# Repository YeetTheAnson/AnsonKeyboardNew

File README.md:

# Anson's Keyboard
This is a generic looking 80% TKL keyboard I made over the span of a month. In total, I've spent about 20-25 hours in total for PCB redesigns, writing the keyboard firmware and case redesigns.

## Features
- Individually backlit keys with software addressable RGB
- 0.91" OLED display
- USB and Bluetooth connectivity

### LED Control
The keyboard has three LED modes:
1. **Off Mode**: All LEDs are turned off
2. **RGB Mode**: LEDs display a rainbow effect
3. **Custom Color Mode**: All LEDs use a user-defined color

### LED Mode Controls
* **Toggle LED Mode**: `Ctrl + Alt + Pause/Break`
   * Cycles through Off → RGB → Custom Color
* **Adjust Brightness Up**: `Ctrl + Alt + Shift + Up Arrow`
* **Adjust Brightness Down**: `Ctrl + Alt + Shift + Down Arrow`

### Custom Color Configuration
1. **Enter Custom Color Mode**: `Ctrl + Alt + Page Up`
2. When in custom color mode:
   * The OLED will prompt for R, G, and B values sequentially
   * Use number keys (0-9) to enter a value between 0-255
   * Press `Backspace` to delete the last digit
   * Press `Enter` to confirm and move to the next color component
   * After setting all three RGB values, the keyboard returns to normal operation with your custom color

### Bluetooth Functionality
The keyboard can operate in either USB or Bluetooth mode:
* **Check Current Mode**: The OLED screen displays either "USB Mode" or "BT Mode"
* **Switch to Bluetooth Mode**: Hold the Pause/Break key during boot (pin IO36)
   * Note: After setup, the keyboard will remain in Bluetooth mode until changed

### OLED Display
The OLED display shows:
1. "AnsonKeyboard"
2. Connection mode (USB or Bluetooth)
3. Current WPM (words per minute) typing speed
4. Current LED mode

When in custom color configuration mode, the display shows prompts for entering RGB values.

### Performance Monitoring
The keyboard automatically calculates your typing speed (WPM) and displays it on the OLED screen. This is calculated based on:
* Number of keypresses
* Time elapsed since last keypress
* Standard conversion (5 characters = 1 word)

### Special Key Combinations
| Function | Key Combination |
|----------|----------------|
| Toggle LED Mode | Ctrl + Alt + Pause/Break |
| Enter Custom Color Mode | Ctrl + Alt + Page Up |
| Increase LED Brightness | Ctrl + Alt + Shift + Up Arrow |
| Decrease LED Brightness | Ctrl + Alt + Shift + Down Arrow |
| Enter Bluetooth Mode | Hold Pause/Break during boot |

## Design Process
I started with a simple idea which was a flat minimalistic TKL keyboard (inspired by the Apple keyboard). The goal was to keep it clean and 
modern, and remove unnecessary designs. However, as I thought more about ergonomics, I quickly realized that a completely flat keyboard wouldn't be comfortable at all
to use during typing.

My initial PCB design had borders that were too thick, which also made the case borders too thick, it was quite bulky and uglier than what I wanted

I originally planned to use the Orpheus Pico as the microcontroller. However, due to the large footprint (making the case even bulkier) and the lack of wireless connectivity, I scrapped that idea
and moved on to a new design. At this point, I also decided to make a triangle wedge to set the keyboard at 6 degrees for a better typing experience.

I wanted an integrated USB C port directly on the PCB, but when I redesigned the case and PCB to fit it, I realized that it would be close to impossible for someone with my skill level to hand solder the USB C port and it
would have stuck up at an angle anyway (this stresses the cable)

For the final design, I came up a solution. Instead of mounting the USB C port directly onto the PCB, I would purchase a USB C breakout board instead and connect it via cables to the PCB. 

(This is when the routing hell begins as I reroute the entire thing at least 3 times)
The first time was my extremely inefficient matrix which was a 8x11 matrix. The traces were extremely messy and I've counted about 1.1k traces and 500 vias in total. (I'm so glad I don't have to see it again). I've then updated it to a 7x14 matrix which made routing much easier.
The second time was when I had to move all LEDs down by 2mm since they didn't align with the cutout in the switches.
Not even an hour after posting about my rerouting, someone from Slack recommmended that I wire my LEDs from top to bottom instead of side to side as to reduce via usage. This is the current version of the PCB and I'm quite happy with it

# Pictures
## Schematic

## PCB

## Renders

## Case Stand (CaseStand.step)

## Lower Case (LowerCase.step)

## Plate (Plate.step)

## Top Case (TopCase.step)

# Bill Of Material

## Electronics (LCSC)

### Passive Components

| QTY  | Name          | Part Number         | LCSC Part Number | Price |
|------|--------------|---------------------|------------------|-------|
| 100x | 4.7kΩ Resistor | 1206W4F4701T5E     | [C17936](https://www.lcsc.com/product-detail/Chip-Resistor-Surface-Mount_UNI-ROYAL-Uniroyal-Elec-1206W4F4701T5E_C17936.html) | $0.32 |
| 100x | 5.1kΩ Resistor | 1206W4F5101T5E     | [C26033](https://www.lcsc.com/product-detail/Chip-Resistor-Surface-Mount_UNI-ROYAL-Uniroyal-Elec-1206W4F5101T5E_C26033.html) | $0.32 |
| 20x  | Tact Switch   | TS-1187A-B-A-B      | [C318884](https://www.lcsc.com/product-detail/Tactile-Switches_XKB-Connection-TS-1187A-B-A-B_C318884.html) | $0.38 |
| 5x   | 3.3v Regulator | AMS1117-3.3        | [C6186](https://www.lcsc.com/product-detail/Voltage-Regulators-Linear-Low-Drop-Out-LDO-Regulators_Advanced-Monolithic-Systems-AMS1117-3-3_C6186.html) | $0.84 |
| 150x | 100nF Capacitor | CC1206KRX7R9BB104  | [C82601](https://www.lcsc.com/product-detail/Multilayer-Ceramic-Capacitors-MLCC-SMD-SMT_YAGEO-CC1206KRX7R9BB104_C82601.html) | $1.61 |
| 20x  | 10uF Capacitor | CL31B106KAHNNNE    | [C14860](https://www.lcsc.com/product-detail/Multilayer-Ceramic-Capacitors-MLCC-SMD-SMT_Samsung-Electro-Mechanics-CL31B106KAHNNNE_C14860.html) | $0.54 |
| 200x | Diode         | 1N4148WL            | [C33962554](https://www.lcsc.com/product-detail/Diodes-General-Purpose_Slkor-SLKORMICRO-Elec-1N4148WL_C33962554.html) | $1.00 |

### Active Components

| QTY  | Name         | Part Number          | LCSC Part Number | Price |
|------|-------------|----------------------|------------------|-------|
| 150x | RGB LED     | SK6812MINI-E         | [C5149201](https://www.lcsc.com/product-detail/RGB-LEDs-Built-in-IC_OPSCO-Optoelectronics-SK6812MINI-E_C5149201.html) | $8.70 |
| 1x   | ESP-32-S3   | ESP32-S3-WROOM-1-N16R2 | [C2913205](https://www.lcsc.com/product-detail/WiFi-Modules_Espressif-Systems-ESP32-S3-WROOM-1-N16R2_C2913205.html) | $5.04 |
| 10x  | Level Shifter | SN74LV1T34DBVR      | [C100024](https://www.lcsc.com/product-detail/Buffers-Drivers-Receivers-Transceivers_Texas-Instruments-SN74LV1T34DBVR_C100024.html) | $0.59 |

**LCSC Shipping**: Singapore Post – $5.72  

## Electronics (Local Vendor. I will be paying for these)

| QTY  | Name | Local Price | Conversion Upcharge | Price |
|------|------|------------|---------------------|-------|
| 5x   | [USB C Breakout Board](https://shopee.com.my/product/145270449/29272008539) | RM8.13 | +$0.15 | $2.10 |
| 1x  | [0.91" OLED](https://shopee.com.my/product/145270449/4639327724) | RM10.62 | +$0.15 | $2.65 |
| 1x   | SPX Express Shipping | RM5.20 | +$0.15 | $1.40 |

---

## Production  

| QTY  | Name       | File Name      | Production Method | Price  |
|------|-----------|---------------|------------------|--------|
| 1x   | Top Case  | TopCase.step  | FDM 3D Print    | -      |
| 1x   | Plate     | Plate.step    | FDM 3D Print    | -      |
| 1x   | Lower Case | LowerCase.step | FDM 3D Print    | -      |
| 1x   | Case Stand | CaseStand.step | FDM 3D Print    | -      |
| 5x   | PCB       | gerbers.zip   | JLCPCB          | $22.20 |
| 1x   | PCB Shipping | -          | E-Post         | $9.76 |

---

## Fasteners  

| QTY  | Name | Local Price | Conversion Upcharge | Price |
|------|------|------------|---------------------|-------|
| 27x  | [M2 x 3.5 x 4 Heat Set Insert](https://shopee.com.my/-M2-M2.5-M3-Helical-Knurled-Embedded-Nut-Heat-Set-Threaded-Insert-3D-Printing-Injection-Molding-Laptop-Repair-Brass-i.327548229.21958741418) | RM9.45 | +$0.15 | $2.39 |
| 12x  | [M2 x 3.5 x 2 Heat Set Insert](https://shopee.com.my/-M2-M2.5-M3-Helical-Knurled-Embedded-Nut-Heat-Set-Threaded-Insert-3D-Printing-Injection-Molding-Laptop-Repair-Brass-i.327548229.21958741418) | RM4.20 | +$0.15 | $1.14 |
| 12x  | [M2 x 5mm Hex Screw](https://shopee.com.my/M2-M2.5-Hex-Socket-Button-Head-Cap-Screw-Allen-Key-Bolt-Skru-Stainless-Steel-304-i.327548229.14990997313) | RM4.56 | +$0.15 | $1.23 |
| 12x  | [M2 x 3mm Hex Screw](https://shopee.com.my/M2-M2.5-Hex-Socket-Button-Head-Cap-Screw-Allen-Key-Bolt-Skru-Stainless-Steel-304-i.327548229.14990997313) | RM4.08 | +$0.15 | $1.12 |
| 15x  | [M2 x 12mm Hex Screw](https://shopee.com.my/M2-M2.5-Hex-Socket-Button-Head-Cap-Screw-Allen-Key-Bolt-Skru-Stainless-Steel-304-i.327548229.14990997313) | RM6.90 | +$0.15 | $1.78 |
| 1x   | SPX Express Shipping | RM10.60 | +$0.15 | $2.66 |

---

## Mechanical  

| QTY  | Name | Local Price | Conversion Upcharge | Price |
|------|------|------------|---------------------|-------|
| 1x   | [XDA Keycap Set](https://shopee.com.my/MKB-Cinnamoroll-Sanrio-PBT-XDA-Profile-Keycap-Set-for-Mechanical-Keyboard-i.72068395.18262626381?sp_atk=5d020f62-27a6-4ec2-9bfb-f2d231a9ee17&xptdk=5d020f62-27a6-4ec2-9bfb-f2d231a9ee17) | RM91.20 | +$2.50 | $24.14 |
| 1x   | [TX Almost Perfect Stabilizers](https://shopee.com.my/product/72068395/18489170375) | RM74.80 | +$2.50 | $20.25 |
| 91x  | [Gateron Smoothie Switches](https://shopee.com.my/product/72068395/14635071158) | RM136.50 | +$4.00 | $35.42 |
| 1x   | SPX Express Shipping | RM17.00 | +$0.40  | $4.31 |

---

## Total Costs  

- **LCSC Total**: $25.06  
- **Electronics (Local) Total**: $6.15
- **JLCPCB Total**: $31.96  
- **Fasteners Total**: $10.32  
- **Mechanical Total**: $84.12  

## **Grand Total: $157.61**

**Note:** Conversion upcharge is just a buffer for conversion rate fluctuations. Any unused funds will be returned.

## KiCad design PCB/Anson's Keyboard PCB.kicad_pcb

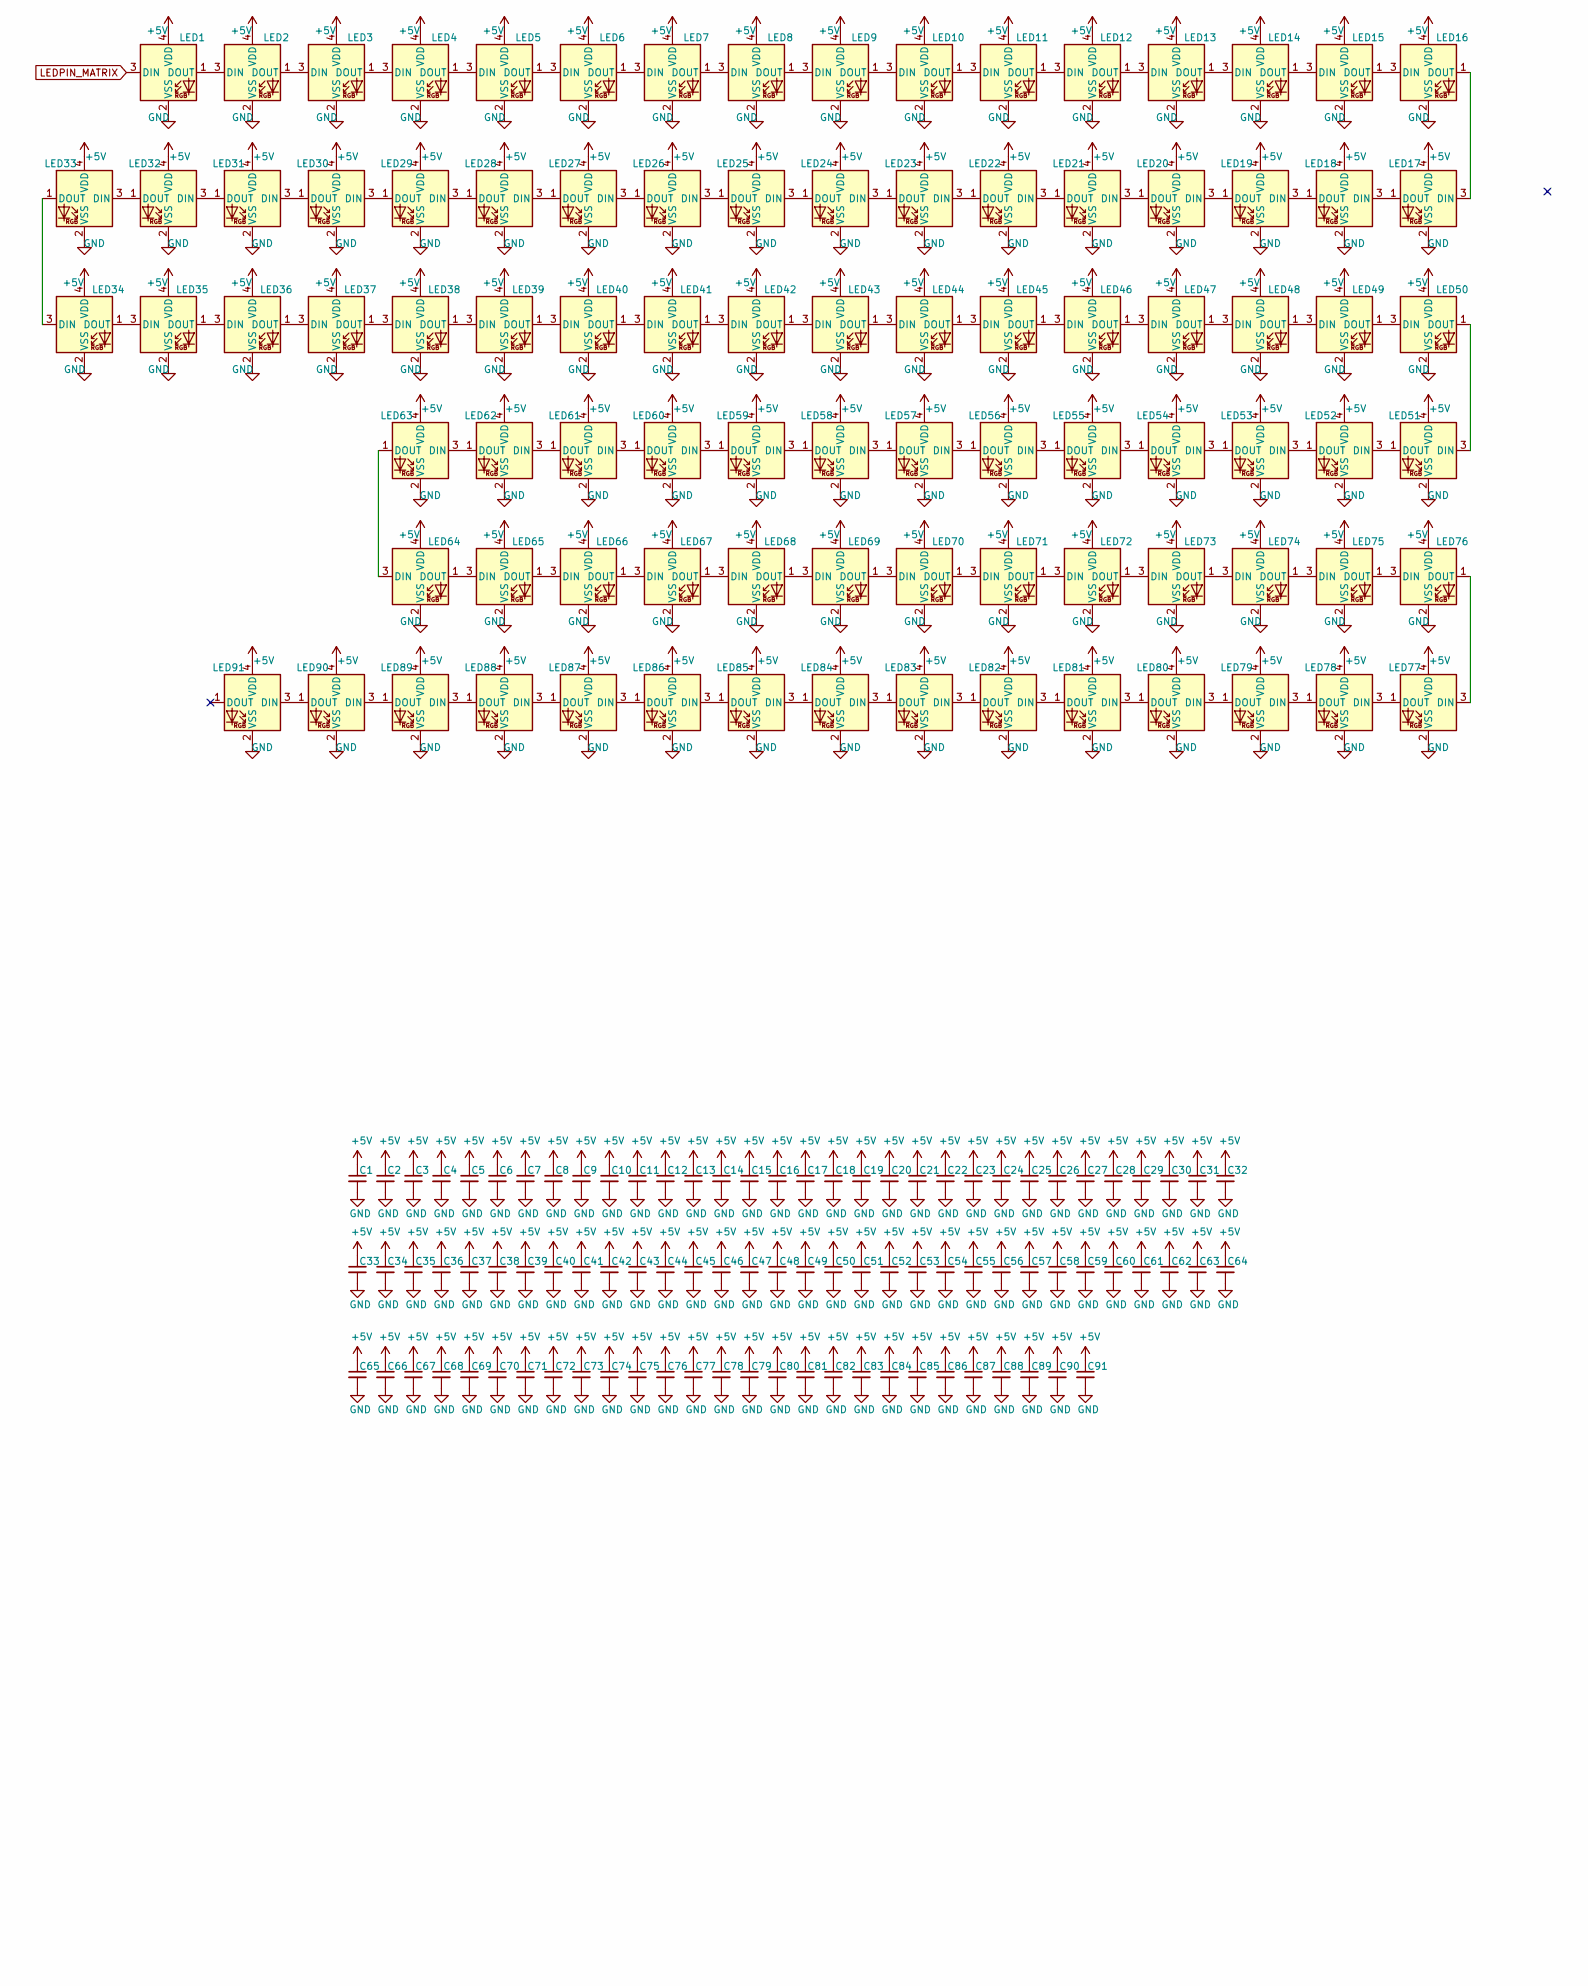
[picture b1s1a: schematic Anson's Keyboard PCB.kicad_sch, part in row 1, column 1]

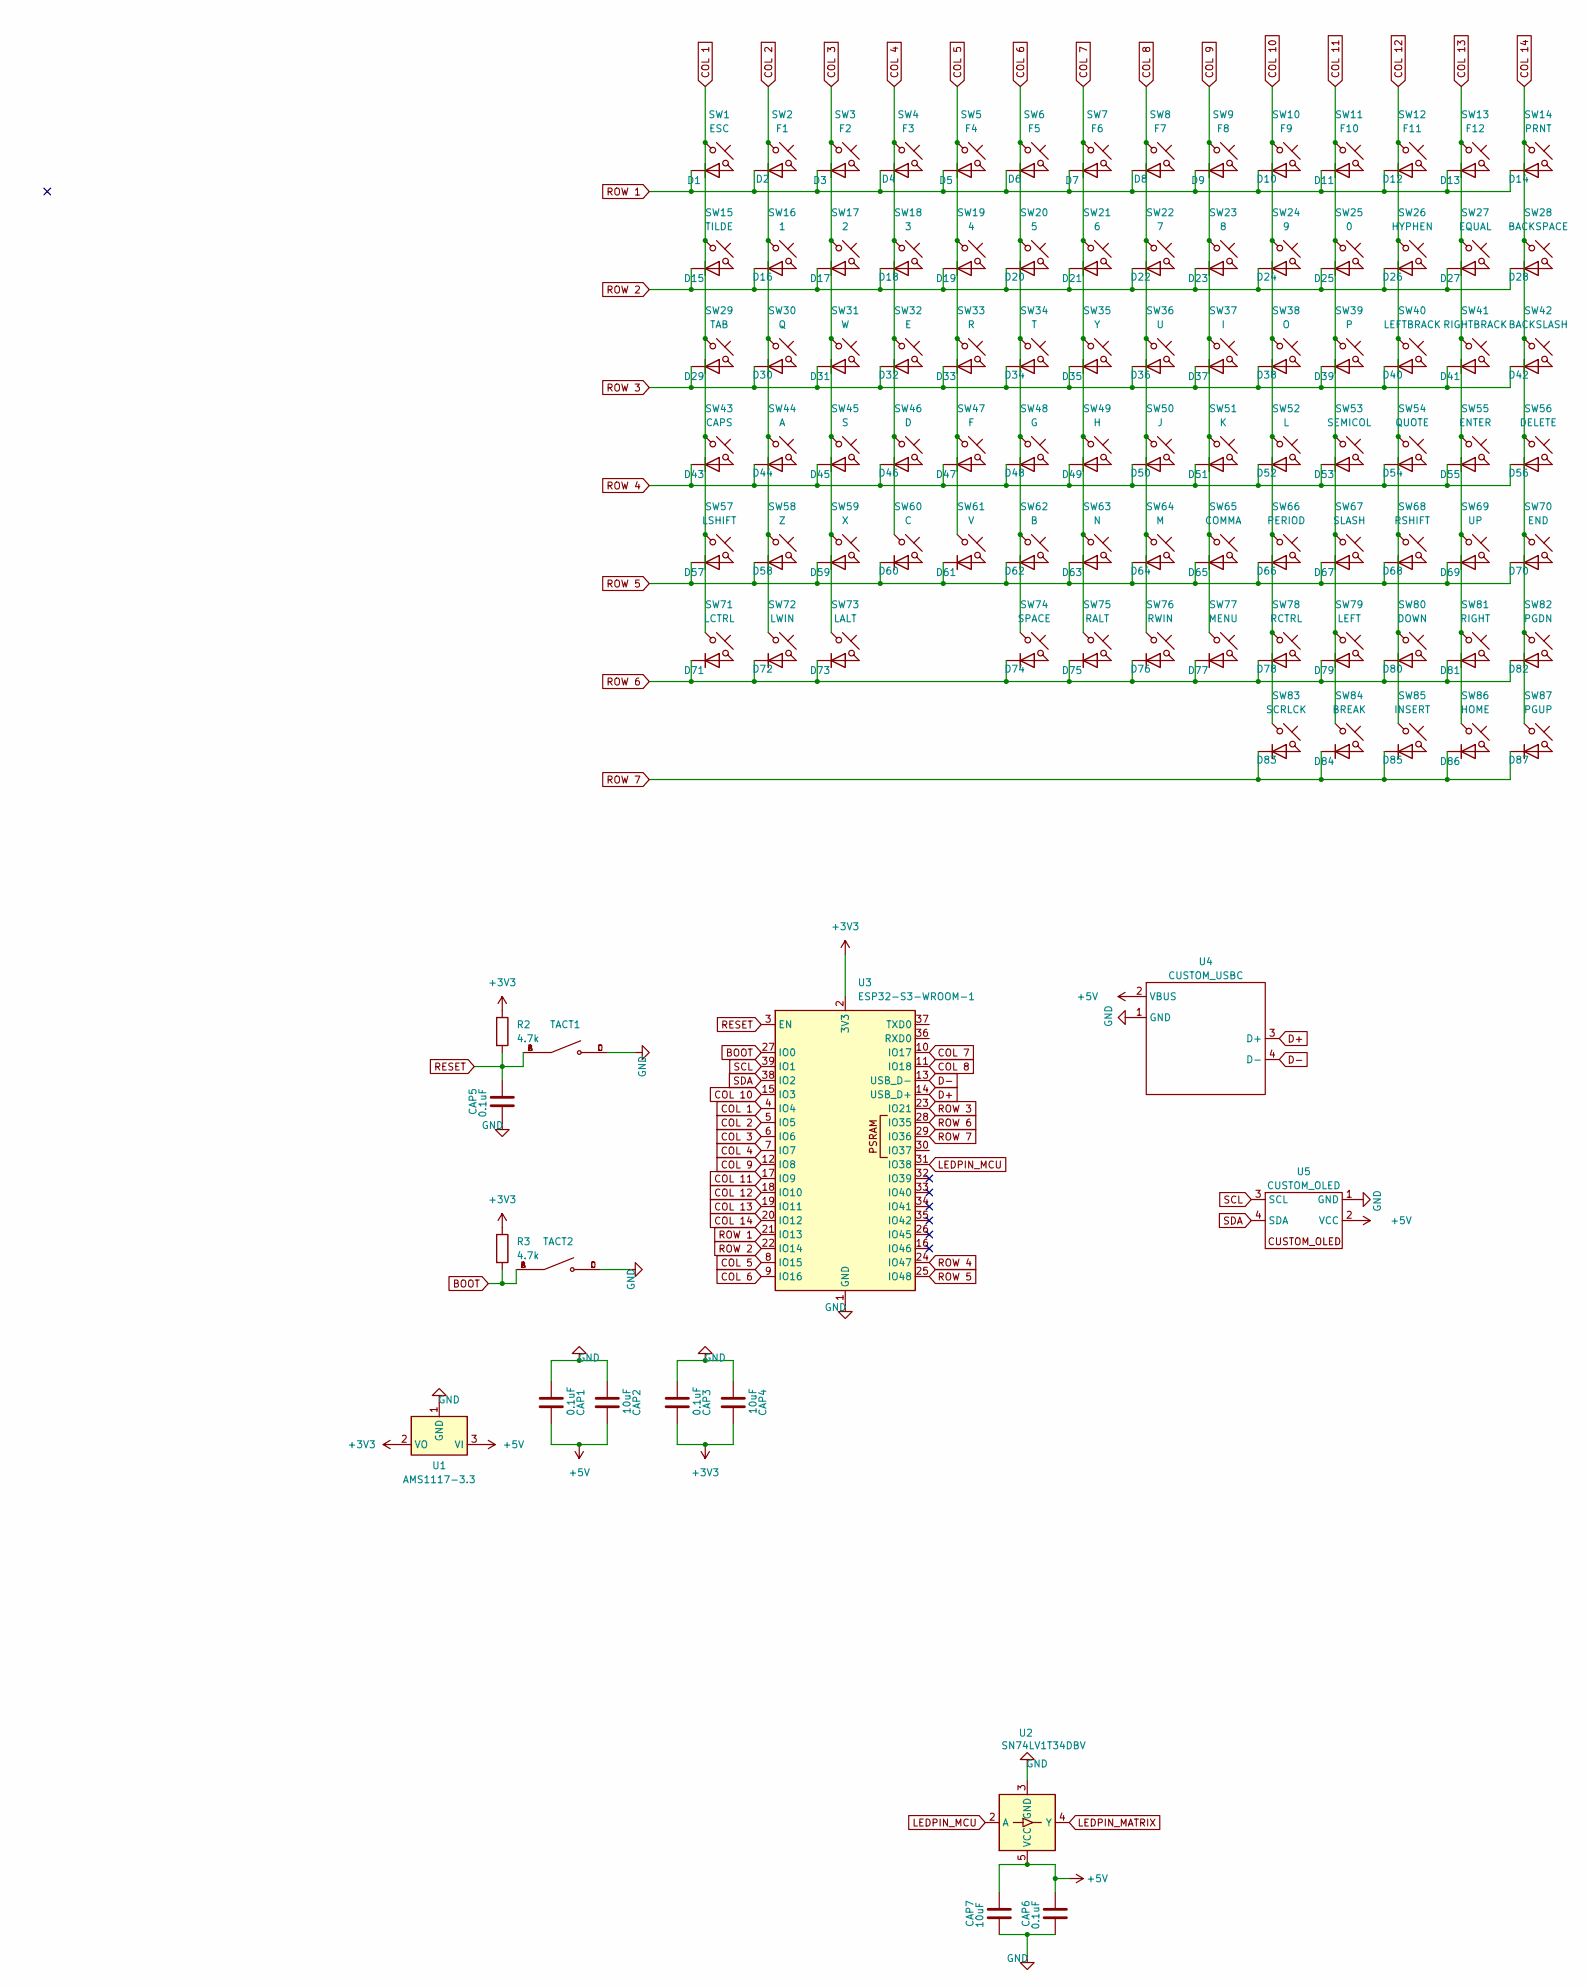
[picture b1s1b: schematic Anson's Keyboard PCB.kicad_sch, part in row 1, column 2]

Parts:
C1, C2, C3, C4, C5, C6, C7, C8, C9, C10, C11, C12, C13, C14, C15, C16, C17, C18, C19, C20, C21, C22, C23, C24, C25, C26, C27, C28, C29, C30, C31, C32, C33, C34, C35, C36, C37, C38, C39, C40, C41, C42, C43, C44, C45, C46, C47, C48, C49, C50, C51, C52, C53, C54, C55, C56, C57, C58, C59, C60, C61, C62, C63, C64, C65, C66, C67, C68, C69, C70, C71, C72, C73, C74, C75, C76, C77, C78, C79, C80, C81, C82, C83, C84, C85, C86, C87, C88, C89, C90, C91: 0.1uF; C_1206_3216Metric_Pad1.33x1.80mm_HandSolder
CAP1, CAP3, CAP5, CAP6: 0.1uF; C_1206_3216Metric_Pad1.33x1.80mm_HandSolder
CAP2, CAP4, CAP7: 10uF; C_1206_3216Metric_Pad1.33x1.80mm_HandSolder
D1, D2, D3, D4, D5, D6, D7, D8, D9, D10, D11, D12, D13, D14, D15, D16, D17, D18, D19, D20, D21, D22, D23, D24, D25, D26, D27, D28, D29, D30, D31, D32, D33, D34, D35, D36, D37, D38, D39, D40, D41, D42, D43, D44, D45, D46, D47, D48, D49, D50, D51, D52, D53, D54, D55, D56, D57, D58, D59, D60, D61, D62, D63, D64, D65, D66, D67, D68, D69, D70, D71, D72, D73, D74, D75, D76, D77, D78, D79, D80, D81, D82, D83, D84, D85, D86, D87: D; D_SOD-123F
LED1, LED2, LED3, LED4, LED5, LED6, LED7, LED8, LED9, LED10, LED11, LED12, LED13, LED14, LED15, LED16, LED17, LED18, LED19, LED20, LED21, LED22, LED23, LED24, LED25, LED26, LED27, LED28, LED29, LED30, LED31, LED32, LED33, LED34, LED35, LED36, LED37, LED38, LED39, LED40, LED41, LED42, LED43, LED44, LED45, LED46, LED47, LED48, LED49, LED50, LED51, LED52, LED53, LED54, LED55, LED56, LED57, LED58, LED59, LED60, LED61, LED62, LED63, LED64, LED65, LED66, LED67, LED68, LED69, LED70, LED71, LED72, LED73, LED74, LED75, LED76, LED77, LED78, LED79, LED80, LED81, LED82, LED83, LED84, LED85, LED86, LED87, LED88, LED89, LED90, LED91: SK6812MINI; SK6812MINI-E
R2, R3: 4.7k; R_1206_3216Metric_Pad1.30x1.75mm_HandSolder
SW1: ESC; SW_Hotswap_Kailh_MX_Plated_1.00u
SW2: F1; SW_Hotswap_Kailh_MX_Plated_1.00u
SW3: F2; SW_Hotswap_Kailh_MX_Plated_1.00u
SW4: F3; SW_Hotswap_Kailh_MX_Plated_1.00u
SW5: F4; SW_Hotswap_Kailh_MX_Plated_1.00u
SW6: F5; SW_Hotswap_Kailh_MX_Plated_1.00u
SW7: F6; SW_Hotswap_Kailh_MX_Plated_1.00u
SW8: F7; SW_Hotswap_Kailh_MX_Plated_1.00u
SW9: F8; SW_Hotswap_Kailh_MX_Plated_1.00u
SW10: F9; SW_Hotswap_Kailh_MX_Plated_1.00u
SW11: F10; SW_Hotswap_Kailh_MX_Plated_1.00u
SW12: F11; SW_Hotswap_Kailh_MX_Plated_1.00u
SW13: F12; SW_Hotswap_Kailh_MX_Plated_1.00u
SW14: PRNT; SW_Hotswap_Kailh_MX_Plated_1.00u
SW15: TILDE; SW_Hotswap_Kailh_MX_Plated_1.00u
SW16: 1; SW_Hotswap_Kailh_MX_Plated_1.00u
SW17: 2; SW_Hotswap_Kailh_MX_Plated_1.00u
SW18: 3; SW_Hotswap_Kailh_MX_Plated_1.00u
SW19: 4; SW_Hotswap_Kailh_MX_Plated_1.00u
SW20: 5; SW_Hotswap_Kailh_MX_Plated_1.00u
SW21: 6; SW_Hotswap_Kailh_MX_Plated_1.00u
SW22: 7; SW_Hotswap_Kailh_MX_Plated_1.00u
SW23: 8; SW_Hotswap_Kailh_MX_Plated_1.00u
SW24: 9; SW_Hotswap_Kailh_MX_Plated_1.00u
SW25: 0; SW_Hotswap_Kailh_MX_Plated_1.00u
SW26: HYPHEN; SW_Hotswap_Kailh_MX_Plated_1.00u
SW27: EQUAL; SW_Hotswap_Kailh_MX_Plated_1.00u
SW28: BACKSPACE; SW_Hotswap_Kailh_MX_Plated_2.00u
SW29: TAB; SW_Hotswap_Kailh_MX_Plated_1.50u
SW30: Q; SW_Hotswap_Kailh_MX_Plated_1.00u
SW31: W; SW_Hotswap_Kailh_MX_Plated_1.00u
SW32: E; SW_Hotswap_Kailh_MX_Plated_1.00u
SW33: R; SW_Hotswap_Kailh_MX_Plated_1.00u
SW34: T; SW_Hotswap_Kailh_MX_Plated_1.00u
SW35: Y; SW_Hotswap_Kailh_MX_Plated_1.00u
SW36: U; SW_Hotswap_Kailh_MX_Plated_1.00u
SW37: I; SW_Hotswap_Kailh_MX_Plated_1.00u
SW38: O; SW_Hotswap_Kailh_MX_Plated_1.00u
SW39: P; SW_Hotswap_Kailh_MX_Plated_1.00u
SW40: LEFTBRACK; SW_Hotswap_Kailh_MX_Plated_1.00u
SW41: RIGHTBRACK; SW_Hotswap_Kailh_MX_Plated_1.00u
SW42: BACKSLASH; SW_Hotswap_Kailh_MX_Plated_1.50u
SW43: CAPS; SW_Hotswap_Kailh_MX_Plated_1.75u
SW44: A; SW_Hotswap_Kailh_MX_Plated_1.00u
SW45: S; SW_Hotswap_Kailh_MX_Plated_1.00u
SW46: D; SW_Hotswap_Kailh_MX_Plated_1.00u
SW47: F; SW_Hotswap_Kailh_MX_Plated_1.00u
SW48: G; SW_Hotswap_Kailh_MX_Plated_1.00u
SW49: H; SW_Hotswap_Kailh_MX_Plated_1.00u
SW50: J; SW_Hotswap_Kailh_MX_Plated_1.00u
SW51: K; SW_Hotswap_Kailh_MX_Plated_1.00u
SW52: L; SW_Hotswap_Kailh_MX_Plated_1.00u
SW53: SEMICOL; SW_Hotswap_Kailh_MX_Plated_1.00u
SW54: QUOTE; SW_Hotswap_Kailh_MX_Plated_1.00u
SW55: ENTER; SW_Hotswap_Kailh_MX_Plated_2.25u
SW56: DELETE; SW_Hotswap_Kailh_MX_Plated_1.00u
SW57: LSHIFT; SW_Hotswap_Kailh_MX_Plated_2.25u
SW58: Z; SW_Hotswap_Kailh_MX_Plated_1.00u
SW59: X; SW_Hotswap_Kailh_MX_Plated_1.00u
SW60: C; SW_Hotswap_Kailh_MX_Plated_1.00u
SW61: V; SW_Hotswap_Kailh_MX_Plated_1.00u
SW62: B; SW_Hotswap_Kailh_MX_Plated_1.00u
SW63: N; SW_Hotswap_Kailh_MX_Plated_1.00u
SW64: M; SW_Hotswap_Kailh_MX_Plated_1.00u
SW65: COMMA; SW_Hotswap_Kailh_MX_Plated_1.00u
SW66: PERIOD; SW_Hotswap_Kailh_MX_Plated_1.00u
SW67: SLASH; SW_Hotswap_Kailh_MX_Plated_1.00u
SW68: RSHIFT; SW_Hotswap_Kailh_MX_Plated_2.75u
SW69: UP; SW_Hotswap_Kailh_MX_Plated_1.00u
SW70: END; SW_Hotswap_Kailh_MX_Plated_1.00u
SW71: LCTRL; SW_Hotswap_Kailh_MX_Plated_1.25u
SW72: LWIN; SW_Hotswap_Kailh_MX_Plated_1.25u
SW73: LALT; SW_Hotswap_Kailh_MX_Plated_1.25u
SW74: SPACE; SW_Hotswap_Kailh_MX_Plated_6.25u
SW75: RALT; SW_Hotswap_Kailh_MX_Plated_1.25u
SW76: RWIN; SW_Hotswap_Kailh_MX_Plated_1.25u
SW77: MENU; SW_Hotswap_Kailh_MX_Plated_1.25u
SW78: RCTRL; SW_Hotswap_Kailh_MX_Plated_1.25u
SW79: LEFT; SW_Hotswap_Kailh_MX_Plated_1.00u
SW80: DOWN; SW_Hotswap_Kailh_MX_Plated_1.00u
SW81: RIGHT; SW_Hotswap_Kailh_MX_Plated_1.00u
SW82: PGDN; SW_Hotswap_Kailh_MX_Plated_1.00u
SW83: SCRLCK; SW_Hotswap_Kailh_MX_Plated_1.00u
SW84: BREAK; SW_Hotswap_Kailh_MX_Plated_1.00u
SW85: INSERT; SW_Hotswap_Kailh_MX_Plated_1.00u
SW86: HOME; SW_Hotswap_Kailh_MX_Plated_1.00u
SW87: PGUP; SW_Hotswap_Kailh_MX_Plated_1.00u
TACT1, TACT2: TS-1187A-B-A-B; SW_TS-1187A-B-A-B; PARTREV A0
U1: AMS1117-3.3; SOT-223-3_TabPin2
U2: SN74LV1T34DBV; SOT-23-5
U3: ESP32-S3-WROOM-1
U4: CUSTOM_USBC
U5: CUSTOM_OLED

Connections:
+3V3: CAP3.2, CAP4.2, R2.1, R3.1, U1.2 (VO), U3.2 (3V3)
+5V: C1.1, C2.1, C3.1, C4.1, C5.1, C6.1, C7.1, C8.1, C9.1, C10.1, C11.1, C12.1, C13.1, C14.1, C15.1, C16.1, C17.1, C18.1, C19.1, C20.1, C21.1, C22.1, C23.1, C24.1, C25.1, C26.1, C27.1, C28.1, C29.1, C30.1, C31.1, C32.1, C33.1, C34.1, C35.1, C36.1, C37.1, C38.1, C39.1, C40.1, C41.1, C42.1, C43.1, C44.1, C45.1, C46.1, C47.1, C48.1, C49.1, C50.1, C51.1, C52.1, C53.1, C54.1, C55.1, C56.1, C57.1, C58.1, C59.1, C60.1, C61.1, C62.1, C63.1, C64.1, C65.1, C66.1, C67.1, C68.1, C69.1, C70.1, C71.1, C72.1, C73.1, C74.1, C75.1, C76.1, C77.1, C78.1, C79.1, C80.1, C81.1, C82.1, C83.1, C84.1, C85.1, C86.1, C87.1, C88.1, C89.1, C90.1, C91.1, CAP1.2, CAP2.2, CAP6.2, CAP7.2, LED1.4 (VDD), LED2.4 (VDD), LED3.4 (VDD), LED4.4 (VDD), LED5.4 (VDD), LED6.4 (VDD), LED7.4 (VDD), LED8.4 (VDD), LED9.4 (VDD), LED10.4 (VDD), LED11.4 (VDD), LED12.4 (VDD), LED13.4 (VDD), LED14.4 (VDD), LED15.4 (VDD), LED16.4 (VDD), LED17.4 (VDD), LED18.4 (VDD), LED19.4 (VDD), LED20.4 (VDD), LED21.4 (VDD), LED22.4 (VDD), LED23.4 (VDD), LED24.4 (VDD), LED25.4 (VDD), LED26.4 (VDD), LED27.4 (VDD), LED28.4 (VDD), LED29.4 (VDD), LED30.4 (VDD), LED31.4 (VDD), LED32.4 (VDD), LED33.4 (VDD), LED34.4 (VDD), LED35.4 (VDD), LED36.4 (VDD), LED37.4 (VDD), LED38.4 (VDD), LED39.4 (VDD), LED40.4 (VDD), LED41.4 (VDD), LED42.4 (VDD), LED43.4 (VDD), LED44.4 (VDD), LED45.4 (VDD), LED46.4 (VDD), LED47.4 (VDD), LED48.4 (VDD), LED49.4 (VDD), LED50.4 (VDD), LED51.4 (VDD), LED52.4 (VDD), LED53.4 (VDD), LED54.4 (VDD), LED55.4 (VDD), LED56.4 (VDD), LED57.4 (VDD), LED58.4 (VDD), LED59.4 (VDD), LED60.4 (VDD), LED61.4 (VDD), LED62.4 (VDD), LED63.4 (VDD), LED64.4 (VDD), LED65.4 (VDD), LED66.4 (VDD), LED67.4 (VDD), LED68.4 (VDD), LED69.4 (VDD), LED70.4 (VDD), LED71.4 (VDD), LED72.4 (VDD), LED73.4 (VDD), LED74.4 (VDD), LED75.4 (VDD), LED76.4 (VDD), LED77.4 (VDD), LED78.4 (VDD), LED79.4 (VDD), LED80.4 (VDD), LED81.4 (VDD), LED82.4 (VDD), LED83.4 (VDD), LED84.4 (VDD), LED85.4 (VDD), LED86.4 (VDD), LED87.4 (VDD), LED88.4 (VDD), LED89.4 (VDD), LED90.4 (VDD), LED91.4 (VDD), U1.3 (VI), U2.5 (VCC), U4.2 (VBUS), U5.2 (VCC)
BOOT: R3.2, TACT2.A, TACT2.B, U3.27 (IO0)
COL 1: SW1.1, SW15.1, SW29.1, SW43.1, SW57.1, SW71.1, U3.4 (IO4)
COL 2: SW2.1, SW16.1, SW30.1, SW44.1, SW58.1, SW72.1, U3.5 (IO5)
COL 3: SW3.1, SW17.1, SW31.1, SW45.1, SW59.1, SW73.1, U3.6 (IO6)
COL 4: SW4.1, SW18.1, SW32.1, SW46.1, SW60.1, U3.7 (IO7)
COL 5: SW5.1, SW19.1, SW33.1, SW47.1, SW61.1, U3.8 (IO15)
COL 6: SW6.1, SW20.1, SW34.1, SW48.1, SW62.1, SW74.1, U3.9 (IO16)
COL 7: SW7.1, SW21.1, SW35.1, SW49.1, SW63.1, SW75.1, U3.10 (IO17)
COL 8: SW8.1, SW22.1, SW36.1, SW50.1, SW64.1, SW76.1, U3.11 (IO18)
COL 9: SW9.1, SW23.1, SW37.1, SW51.1, SW65.1, SW77.1, U3.12 (IO8)
COL 10: SW10.1, SW24.1, SW38.1, SW52.1, SW66.1, SW78.1, SW83.1, U3.15 (IO3)
COL 11: SW11.1, SW25.1, SW39.1, SW53.1, SW67.1, SW79.1, SW84.1, U3.17 (IO9)
COL 12: SW12.1, SW26.1, SW40.1, SW54.1, SW68.1, SW80.1, SW85.1, U3.18 (IO10)
COL 13: SW13.1, SW27.1, SW41.1, SW55.1, SW69.1, SW81.1, SW86.1, U3.19 (IO11)
COL 14: SW14.1, SW28.1, SW42.1, SW56.1, SW70.1, SW82.1, SW87.1, U3.20 (IO12)
D+: U3.14 (USB_D+), U4.3 (D+)
D-: U3.13 (USB_D-), U4.4 (D-)
GND: C1.2, C2.2, C3.2, C4.2, C5.2, C6.2, C7.2, C8.2, C9.2, C10.2, C11.2, C12.2, C13.2, C14.2, C15.2, C16.2, C17.2, C18.2, C19.2, C20.2, C21.2, C22.2, C23.2, C24.2, C25.2, C26.2, C27.2, C28.2, C29.2, C30.2, C31.2, C32.2, C33.2, C34.2, C35.2, C36.2, C37.2, C38.2, C39.2, C40.2, C41.2, C42.2, C43.2, C44.2, C45.2, C46.2, C47.2, C48.2, C49.2, C50.2, C51.2, C52.2, C53.2, C54.2, C55.2, C56.2, C57.2, C58.2, C59.2, C60.2, C61.2, C62.2, C63.2, C64.2, C65.2, C66.2, C67.2, C68.2, C69.2, C70.2, C71.2, C72.2, C73.2, C74.2, C75.2, C76.2, C77.2, C78.2, C79.2, C80.2, C81.2, C82.2, C83.2, C84.2, C85.2, C86.2, C87.2, C88.2, C89.2, C90.2, C91.2, CAP1.1, CAP2.1, CAP3.1, CAP4.1, CAP5.1, CAP6.1, CAP7.1, LED1.2 (VSS), LED2.2 (VSS), LED3.2 (VSS), LED4.2 (VSS), LED5.2 (VSS), LED6.2 (VSS), LED7.2 (VSS), LED8.2 (VSS), LED9.2 (VSS), LED10.2 (VSS), LED11.2 (VSS), LED12.2 (VSS), LED13.2 (VSS), LED14.2 (VSS), LED15.2 (VSS), LED16.2 (VSS), LED17.2 (VSS), LED18.2 (VSS), LED19.2 (VSS), LED20.2 (VSS), LED21.2 (VSS), LED22.2 (VSS), LED23.2 (VSS), LED24.2 (VSS), LED25.2 (VSS), LED26.2 (VSS), LED27.2 (VSS), LED28.2 (VSS), LED29.2 (VSS), LED30.2 (VSS), LED31.2 (VSS), LED32.2 (VSS), LED33.2 (VSS), LED34.2 (VSS), LED35.2 (VSS), LED36.2 (VSS), LED37.2 (VSS), LED38.2 (VSS), LED39.2 (VSS), LED40.2 (VSS), LED41.2 (VSS), LED42.2 (VSS), LED43.2 (VSS), LED44.2 (VSS), LED45.2 (VSS), LED46.2 (VSS), LED47.2 (VSS), LED48.2 (VSS), LED49.2 (VSS), LED50.2 (VSS), LED51.2 (VSS), LED52.2 (VSS), LED53.2 (VSS), LED54.2 (VSS), LED55.2 (VSS), LED56.2 (VSS), LED57.2 (VSS), LED58.2 (VSS), LED59.2 (VSS), LED60.2 (VSS), LED61.2 (VSS), LED62.2 (VSS), LED63.2 (VSS), LED64.2 (VSS), LED65.2 (VSS), LED66.2 (VSS), LED67.2 (VSS), LED68.2 (VSS), LED69.2 (VSS), LED70.2 (VSS), LED71.2 (VSS), LED72.2 (VSS), LED73.2 (VSS), LED74.2 (VSS), LED75.2 (VSS), LED76.2 (VSS), LED77.2 (VSS), LED78.2 (VSS), LED79.2 (VSS), LED80.2 (VSS), LED81.2 (VSS), LED82.2 (VSS), LED83.2 (VSS), LED84.2 (VSS), LED85.2 (VSS), LED86.2 (VSS), LED87.2 (VSS), LED88.2 (VSS), LED89.2 (VSS), LED90.2 (VSS), LED91.2 (VSS), TACT1.C, TACT1.D, TACT2.C, TACT2.D, U1.1 (GND), U2.3 (GND), U3.1 (GND), U3.40 (GND), U3.41 (GND), U4.1 (GND), U5.1 (GND)
LEDPIN_MATRIX: LED1.3 (DIN), U2.4 (Y)
LEDPIN_MCU: U2.2 (A), U3.31 (IO38)
unnamed: D1.2 (A), SW1.2
unnamed: D2.2 (A), SW2.2
unnamed: D3.2 (A), SW3.2
unnamed: D4.2 (A), SW4.2
unnamed: D5.2 (A), SW5.2
unnamed: D6.2 (A), SW6.2
unnamed: D7.2 (A), SW7.2
unnamed: D8.2 (A), SW8.2
unnamed: D9.2 (A), SW9.2
unnamed: D10.2 (A), SW10.2
unnamed: D11.2 (A), SW11.2
unnamed: D12.2 (A), SW12.2
unnamed: D13.2 (A), SW13.2
unnamed: D14.2 (A), SW14.2
unnamed: D15.2 (A), SW15.2
unnamed: D16.2 (A), SW16.2
unnamed: D17.2 (A), SW17.2
unnamed: D18.2 (A), SW18.2
unnamed: D19.2 (A), SW19.2
unnamed: D20.2 (A), SW20.2
unnamed: D21.2 (A), SW21.2
unnamed: D22.2 (A), SW22.2
unnamed: D23.2 (A), SW23.2
unnamed: D24.2 (A), SW24.2
unnamed: D25.2 (A), SW25.2
unnamed: D26.2 (A), SW26.2
unnamed: D27.2 (A), SW27.2
unnamed: D28.2 (A), SW28.2
unnamed: D29.2 (A), SW29.2
unnamed: D30.2 (A), SW30.2
unnamed: D31.2 (A), SW31.2
unnamed: D32.2 (A), SW32.2
unnamed: D33.2 (A), SW33.2
unnamed: D34.2 (A), SW34.2
unnamed: D35.2 (A), SW35.2
unnamed: D36.2 (A), SW36.2
unnamed: D37.2 (A), SW37.2
unnamed: D38.2 (A), SW38.2
unnamed: D39.2 (A), SW39.2
unnamed: D40.2 (A), SW40.2
unnamed: D41.2 (A), SW41.2
unnamed: D42.2 (A), SW42.2
unnamed: D43.2 (A), SW43.2
unnamed: D44.2 (A), SW44.2
unnamed: D45.2 (A), SW45.2
unnamed: D46.2 (A), SW46.2
unnamed: D47.2 (A), SW47.2
unnamed: D48.2 (A), SW48.2
unnamed: D49.2 (A), SW49.2
unnamed: D50.2 (A), SW50.2
unnamed: D51.2 (A), SW51.2
unnamed: D52.2 (A), SW52.2
unnamed: D53.2 (A), SW53.2
unnamed: D54.2 (A), SW54.2
unnamed: D55.2 (A), SW55.2
unnamed: D56.2 (A), SW56.2
unnamed: D57.2 (A), SW57.2
unnamed: D58.2 (A), SW58.2
unnamed: D59.2 (A), SW59.2
unnamed: D60.2 (A), SW60.2
unnamed: D61.2 (A), SW61.2
unnamed: D62.2 (A), SW62.2
unnamed: D63.2 (A), SW63.2
unnamed: D64.2 (A), SW64.2
unnamed: D65.2 (A), SW65.2
unnamed: D66.2 (A), SW66.2
unnamed: D67.2 (A), SW67.2
unnamed: D68.2 (A), SW68.2
unnamed: D69.2 (A), SW69.2
unnamed: D70.2 (A), SW70.2
unnamed: D71.2 (A), SW71.2
unnamed: D72.2 (A), SW72.2
unnamed: D73.2 (A), SW73.2
unnamed: D74.2 (A), SW74.2
unnamed: D75.2 (A), SW75.2
unnamed: D76.2 (A), SW76.2
unnamed: D77.2 (A), SW77.2
unnamed: D78.2 (A), SW78.2
unnamed: D79.2 (A), SW79.2
unnamed: D80.2 (A), SW80.2
unnamed: D81.2 (A), SW81.2
unnamed: D82.2 (A), SW82.2
unnamed: D83.2 (A), SW83.2
unnamed: D84.2 (A), SW84.2
unnamed: D85.2 (A), SW85.2
unnamed: D86.2 (A), SW86.2
unnamed: D87.2 (A), SW87.2
unnamed: LED1.1 (DOUT), LED2.3 (DIN)
unnamed: LED2.1 (DOUT), LED3.3 (DIN)
unnamed: LED3.1 (DOUT), LED4.3 (DIN)
unnamed: LED4.1 (DOUT), LED5.3 (DIN)
unnamed: LED5.1 (DOUT), LED6.3 (DIN)
unnamed: LED6.1 (DOUT), LED7.3 (DIN)
unnamed: LED7.1 (DOUT), LED8.3 (DIN)
unnamed: LED8.1 (DOUT), LED9.3 (DIN)
unnamed: LED9.1 (DOUT), LED10.3 (DIN)
unnamed: LED10.1 (DOUT), LED11.3 (DIN)
unnamed: LED11.1 (DOUT), LED12.3 (DIN)
unnamed: LED12.1 (DOUT), LED13.3 (DIN)
unnamed: LED13.1 (DOUT), LED14.3 (DIN)
unnamed: LED14.1 (DOUT), LED15.3 (DIN)
unnamed: LED15.1 (DOUT), LED16.3 (DIN)
unnamed: LED16.1 (DOUT), LED17.3 (DIN)
unnamed: LED17.1 (DOUT), LED18.3 (DIN)
unnamed: LED18.1 (DOUT), LED19.3 (DIN)
unnamed: LED19.1 (DOUT), LED20.3 (DIN)
unnamed: LED20.1 (DOUT), LED21.3 (DIN)
unnamed: LED21.1 (DOUT), LED22.3 (DIN)
unnamed: LED22.1 (DOUT), LED23.3 (DIN)
unnamed: LED23.1 (DOUT), LED24.3 (DIN)
unnamed: LED24.1 (DOUT), LED25.3 (DIN)
unnamed: LED25.1 (DOUT), LED26.3 (DIN)
unnamed: LED26.1 (DOUT), LED27.3 (DIN)
unnamed: LED27.1 (DOUT), LED28.3 (DIN)
unnamed: LED28.1 (DOUT), LED29.3 (DIN)
unnamed: LED29.1 (DOUT), LED30.3 (DIN)
unnamed: LED30.1 (DOUT), LED31.3 (DIN)
unnamed: LED31.1 (DOUT), LED32.3 (DIN)
unnamed: LED32.1 (DOUT), LED33.3 (DIN)
unnamed: LED33.1 (DOUT), LED34.3 (DIN)
unnamed: LED34.1 (DOUT), LED35.3 (DIN)
unnamed: LED35.1 (DOUT), LED36.3 (DIN)
unnamed: LED36.1 (DOUT), LED37.3 (DIN)
unnamed: LED37.1 (DOUT), LED38.3 (DIN)
unnamed: LED38.1 (DOUT), LED39.3 (DIN)
unnamed: LED39.1 (DOUT), LED40.3 (DIN)
unnamed: LED40.1 (DOUT), LED41.3 (DIN)
unnamed: LED41.1 (DOUT), LED42.3 (DIN)
unnamed: LED42.1 (DOUT), LED43.3 (DIN)
unnamed: LED43.1 (DOUT), LED44.3 (DIN)
unnamed: LED44.1 (DOUT), LED45.3 (DIN)
unnamed: LED45.1 (DOUT), LED46.3 (DIN)
unnamed: LED46.1 (DOUT), LED47.3 (DIN)
unnamed: LED47.1 (DOUT), LED48.3 (DIN)
unnamed: LED48.1 (DOUT), LED49.3 (DIN)
unnamed: LED49.1 (DOUT), LED50.3 (DIN)
unnamed: LED50.1 (DOUT), LED51.3 (DIN)
unnamed: LED51.1 (DOUT), LED52.3 (DIN)
unnamed: LED52.1 (DOUT), LED53.3 (DIN)
unnamed: LED53.1 (DOUT), LED54.3 (DIN)
unnamed: LED54.1 (DOUT), LED55.3 (DIN)
unnamed: LED55.1 (DOUT), LED56.3 (DIN)
unnamed: LED56.1 (DOUT), LED57.3 (DIN)
unnamed: LED57.1 (DOUT), LED58.3 (DIN)
unnamed: LED58.1 (DOUT), LED59.3 (DIN)
unnamed: LED59.1 (DOUT), LED60.3 (DIN)
unnamed: LED60.1 (DOUT), LED61.3 (DIN)
unnamed: LED61.1 (DOUT), LED62.3 (DIN)
unnamed: LED62.1 (DOUT), LED63.3 (DIN)
unnamed: LED63.1 (DOUT), LED64.3 (DIN)
unnamed: LED64.1 (DOUT), LED65.3 (DIN)
unnamed: LED65.1 (DOUT), LED66.3 (DIN)
unnamed: LED66.1 (DOUT), LED67.3 (DIN)
unnamed: LED67.1 (DOUT), LED68.3 (DIN)
unnamed: LED68.1 (DOUT), LED69.3 (DIN)
unnamed: LED69.1 (DOUT), LED70.3 (DIN)
unnamed: LED70.1 (DOUT), LED71.3 (DIN)
unnamed: LED71.1 (DOUT), LED72.3 (DIN)
unnamed: LED72.1 (DOUT), LED73.3 (DIN)
unnamed: LED73.1 (DOUT), LED74.3 (DIN)
unnamed: LED74.1 (DOUT), LED75.3 (DIN)
unnamed: LED75.1 (DOUT), LED76.3 (DIN)
unnamed: LED76.1 (DOUT), LED77.3 (DIN)
unnamed: LED77.1 (DOUT), LED78.3 (DIN)
unnamed: LED78.1 (DOUT), LED79.3 (DIN)
unnamed: LED79.1 (DOUT), LED80.3 (DIN)
unnamed: LED80.1 (DOUT), LED81.3 (DIN)
unnamed: LED81.1 (DOUT), LED82.3 (DIN)
unnamed: LED82.1 (DOUT), LED83.3 (DIN)
unnamed: LED83.1 (DOUT), LED84.3 (DIN)
unnamed: LED84.1 (DOUT), LED85.3 (DIN)
unnamed: LED85.1 (DOUT), LED86.3 (DIN)
unnamed: LED86.1 (DOUT), LED87.3 (DIN)
unnamed: LED87.1 (DOUT), LED88.3 (DIN)
unnamed: LED88.1 (DOUT), LED89.3 (DIN)
unnamed: LED89.1 (DOUT), LED90.3 (DIN)
unnamed: LED90.1 (DOUT), LED91.3 (DIN)
RESET: CAP5.2, R2.2, TACT1.A, TACT1.B, U3.3 (EN)
ROW 1: D1.1 (K), D2.1 (K), D3.1 (K), D4.1 (K), D5.1 (K), D6.1 (K), D7.1 (K), D8.1 (K), D9.1 (K), D10.1 (K), D11.1 (K), D12.1 (K), D13.1 (K), D14.1 (K), U3.21 (IO13)
ROW 2: D15.1 (K), D16.1 (K), D17.1 (K), D18.1 (K), D19.1 (K), D20.1 (K), D21.1 (K), D22.1 (K), D23.1 (K), D24.1 (K), D25.1 (K), D26.1 (K), D27.1 (K), D28.1 (K), U3.22 (IO14)
ROW 3: D29.1 (K), D30.1 (K), D31.1 (K), D32.1 (K), D33.1 (K), D34.1 (K), D35.1 (K), D36.1 (K), D37.1 (K), D38.1 (K), D39.1 (K), D40.1 (K), D41.1 (K), D42.1 (K), U3.23 (IO21)
ROW 4: D43.1 (K), D44.1 (K), D45.1 (K), D46.1 (K), D47.1 (K), D48.1 (K), D49.1 (K), D50.1 (K), D51.1 (K), D52.1 (K), D53.1 (K), D54.1 (K), D55.1 (K), D56.1 (K), U3.24 (IO47)
ROW 5: D57.1 (K), D58.1 (K), D59.1 (K), D60.1 (K), D61.1 (K), D62.1 (K), D63.1 (K), D64.1 (K), D65.1 (K), D66.1 (K), D67.1 (K), D68.1 (K), D69.1 (K), D70.1 (K), U3.25 (IO48)
ROW 6: D71.1 (K), D72.1 (K), D73.1 (K), D74.1 (K), D75.1 (K), D76.1 (K), D77.1 (K), D78.1 (K), D79.1 (K), D80.1 (K), D81.1 (K), D82.1 (K), U3.28 (IO35)
ROW 7: D83.1 (K), D84.1 (K), D85.1 (K), D86.1 (K), D87.1 (K), U3.29 (IO36)
SCL: U3.39 (IO1), U5.3 (SCL)
SDA: U3.38 (IO2), U5.4 (SDA)

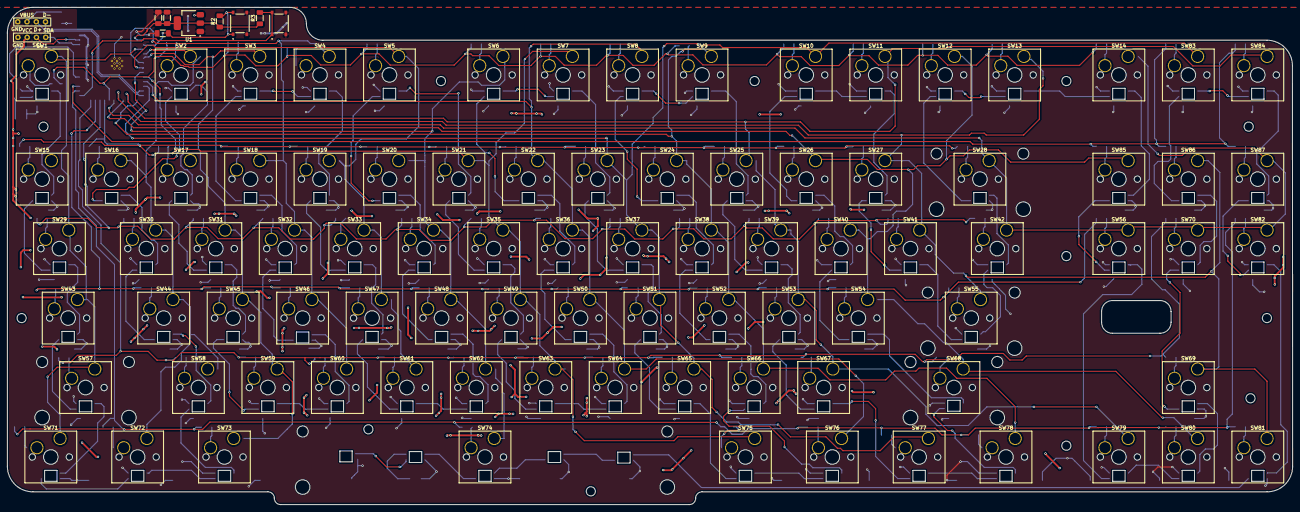
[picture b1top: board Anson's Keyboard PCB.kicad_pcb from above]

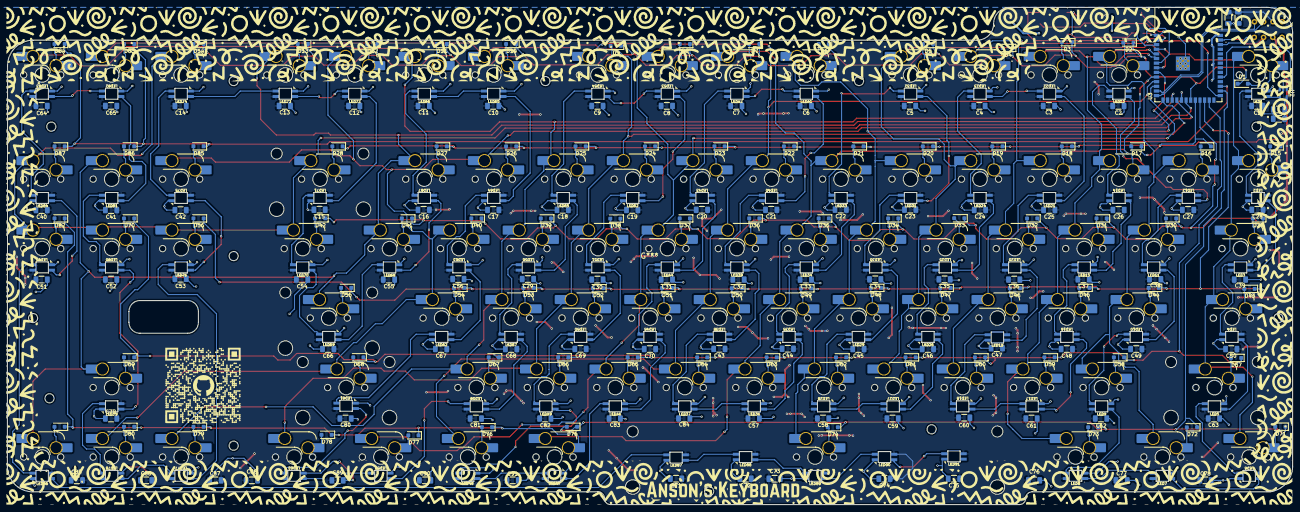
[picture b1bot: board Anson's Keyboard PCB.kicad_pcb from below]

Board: 2 copper layers, 352.5 x 136.4 mm, 372 parts (275 on the bottom side), 209 nets.

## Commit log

2025-10-07 commits
    multiple fixes
2025-10-07 Add bom
    multiple fixes
2025-10-10 Update bom
2025-10-10 Add source design file
2025-10-19 Updated PCB to use hotswap
    Rewired everything to use hotswap sockets instead of direct switch soldering
2025-10-20 Updated for better manufacturability
    Rerouted some parts
2025-10-20 Multiple Changes
    Added more PCB mounting holes
    Changed PCB mounting hole size to M2
    Added updated PCB Gerber
    Added updated PCB 3D model
    Updated assembled .f3z [AWS outage broke Autodesk, currently can't export f3z] and .STEP for new mounting points and changes
    Updated BOM for additional screws and heatset inserts
